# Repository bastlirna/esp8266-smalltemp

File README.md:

# esp8266-smalltemp
Small temperature sensor based on ESP8266 and DHT22

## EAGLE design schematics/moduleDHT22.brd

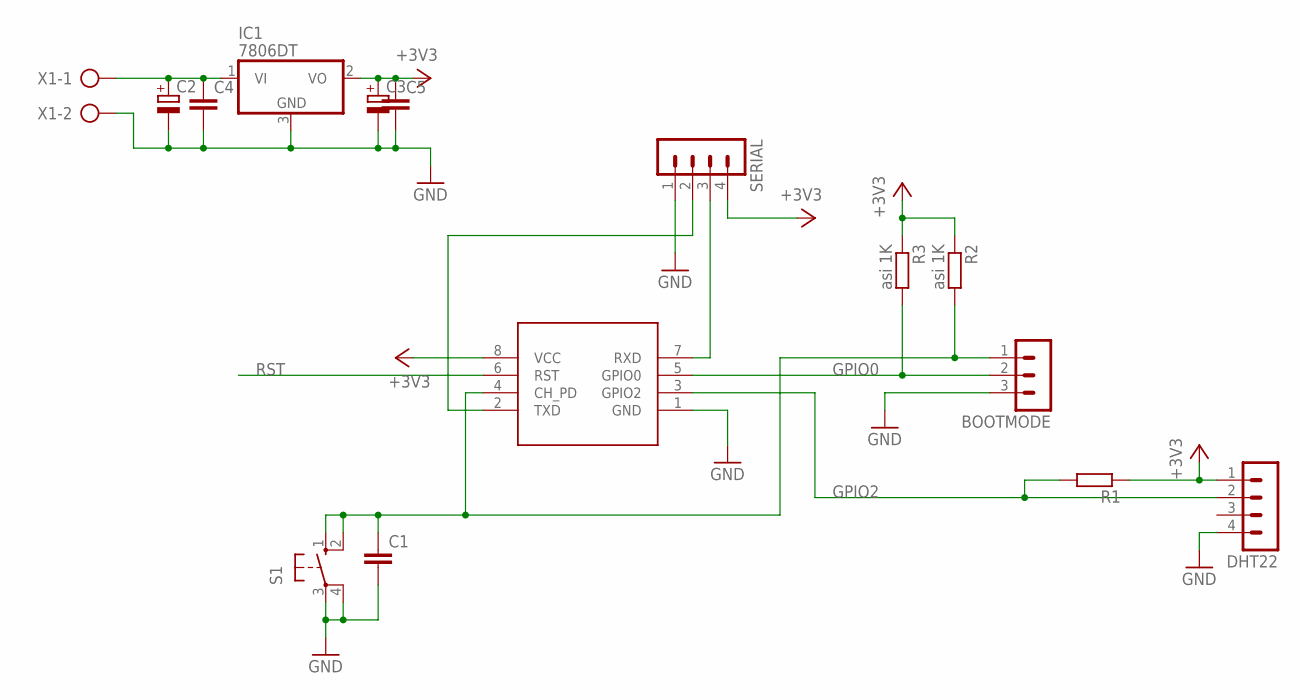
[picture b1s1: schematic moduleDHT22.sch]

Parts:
BOOTMODE: MA03-1
C1, C4, C5: C-EUC0603; C0603
C2, C3: CPOL-EU153CLV-0505; 153CLV-0505
DHT22: MA04-1
IC1: 7806DT; TO252
R1: R-EU_R0603; R0603
R2, R3: asi 1K; R0603
S1: 10-XX; B3F-10XX
SERIAL: MA04-1
U$1: ESP8266-01
X1: AK300/2

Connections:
+3V3: C3.+, C5.1, DHT22.1, IC1.2 (VO), R1.1, R2.1, R3.1, SERIAL.4, U$1.8 (VCC)
GND: BOOTMODE.3, C1.2, C2.-, C3.-, C4.2, C5.2, DHT22.4, IC1.3 (GND), S1.3, S1.4 (P1), SERIAL.1, U$1.1 (GND), X1.2
GPIO0: BOOTMODE.2, R3.2, U$1.5 (GPIO0)
GPIO2: DHT22.2, R1.2, U$1.3 (GPIO2)
unnamed: C2.+, C4.1, IC1.1 (VI), X1.1
unnamed: SERIAL.2, U$1.2 (TXD)
unnamed: SERIAL.3, U$1.7 (RXD)
unnamed: BOOTMODE.1, C1.1, R2.2, S1.1 (S), S1.2 (S1), U$1.4 (CH_PD)
RST: U$1.6 (RST)

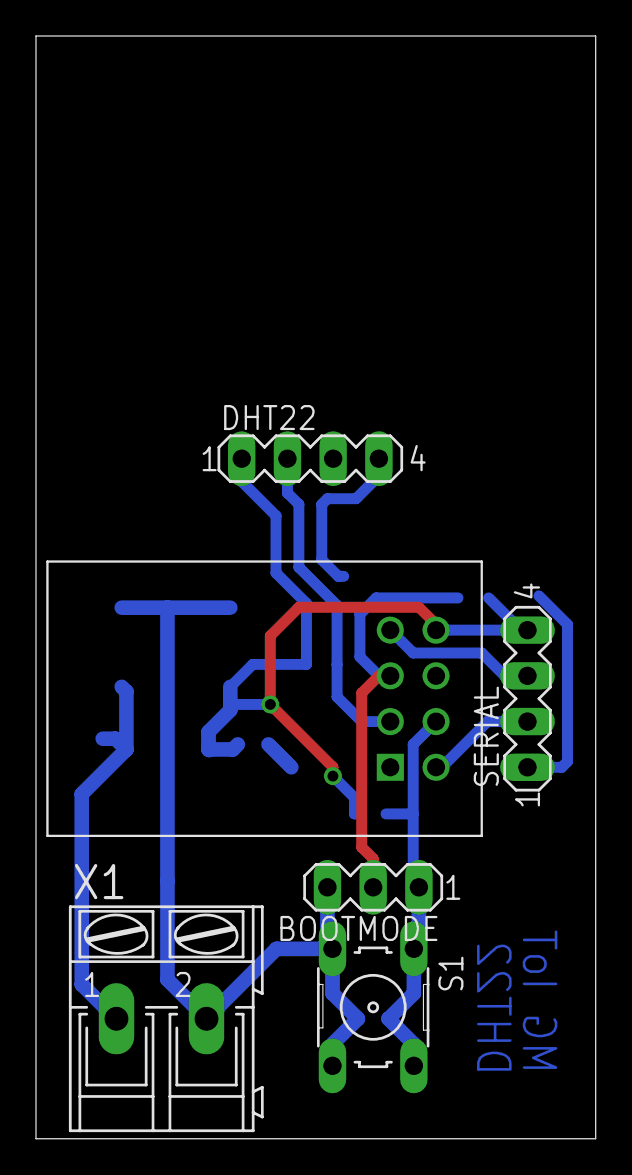
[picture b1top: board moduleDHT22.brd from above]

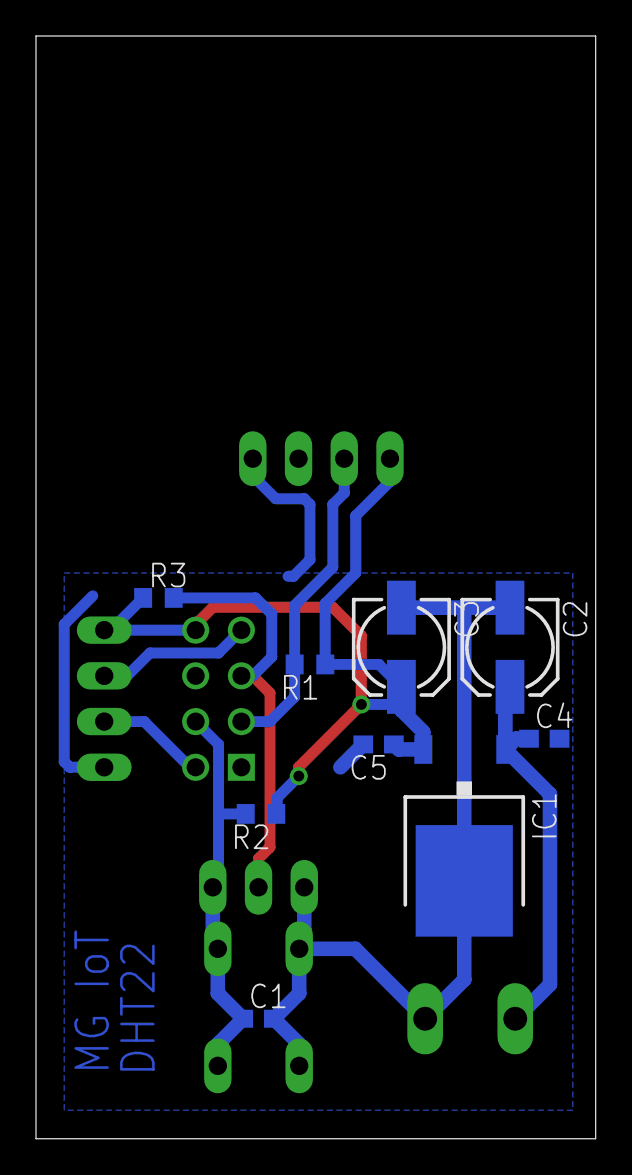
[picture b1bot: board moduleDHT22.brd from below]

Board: 2 copper layers, 31.1 x 61.3 mm, 15 parts (9 on the bottom side), 8 nets.

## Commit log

2016-05-11 add schematics
